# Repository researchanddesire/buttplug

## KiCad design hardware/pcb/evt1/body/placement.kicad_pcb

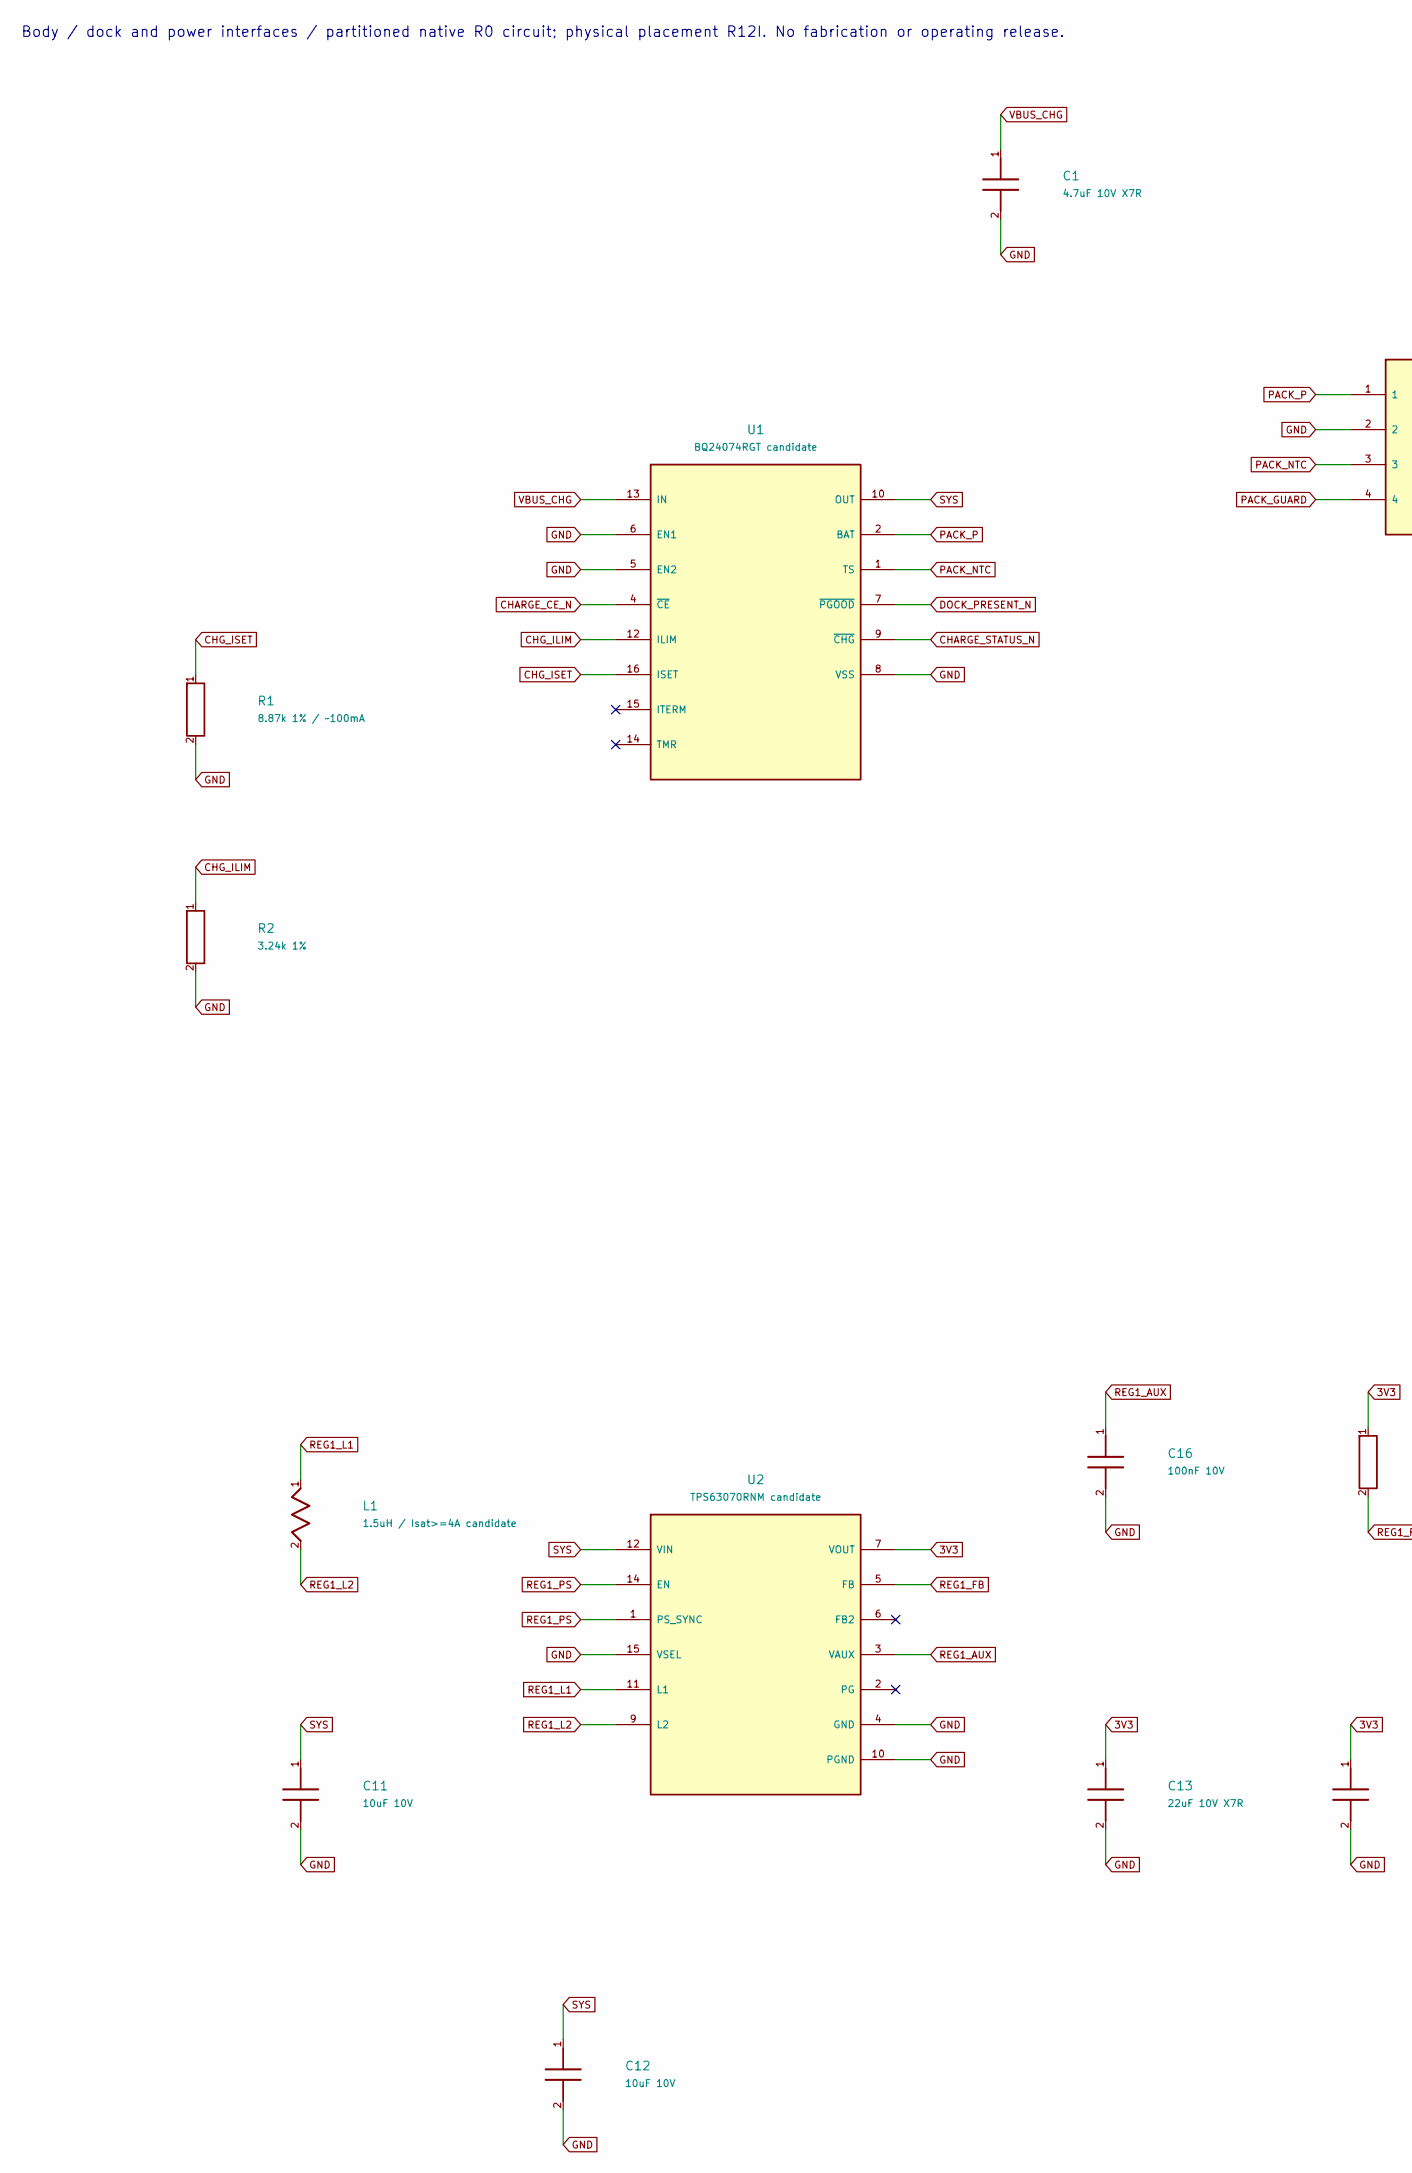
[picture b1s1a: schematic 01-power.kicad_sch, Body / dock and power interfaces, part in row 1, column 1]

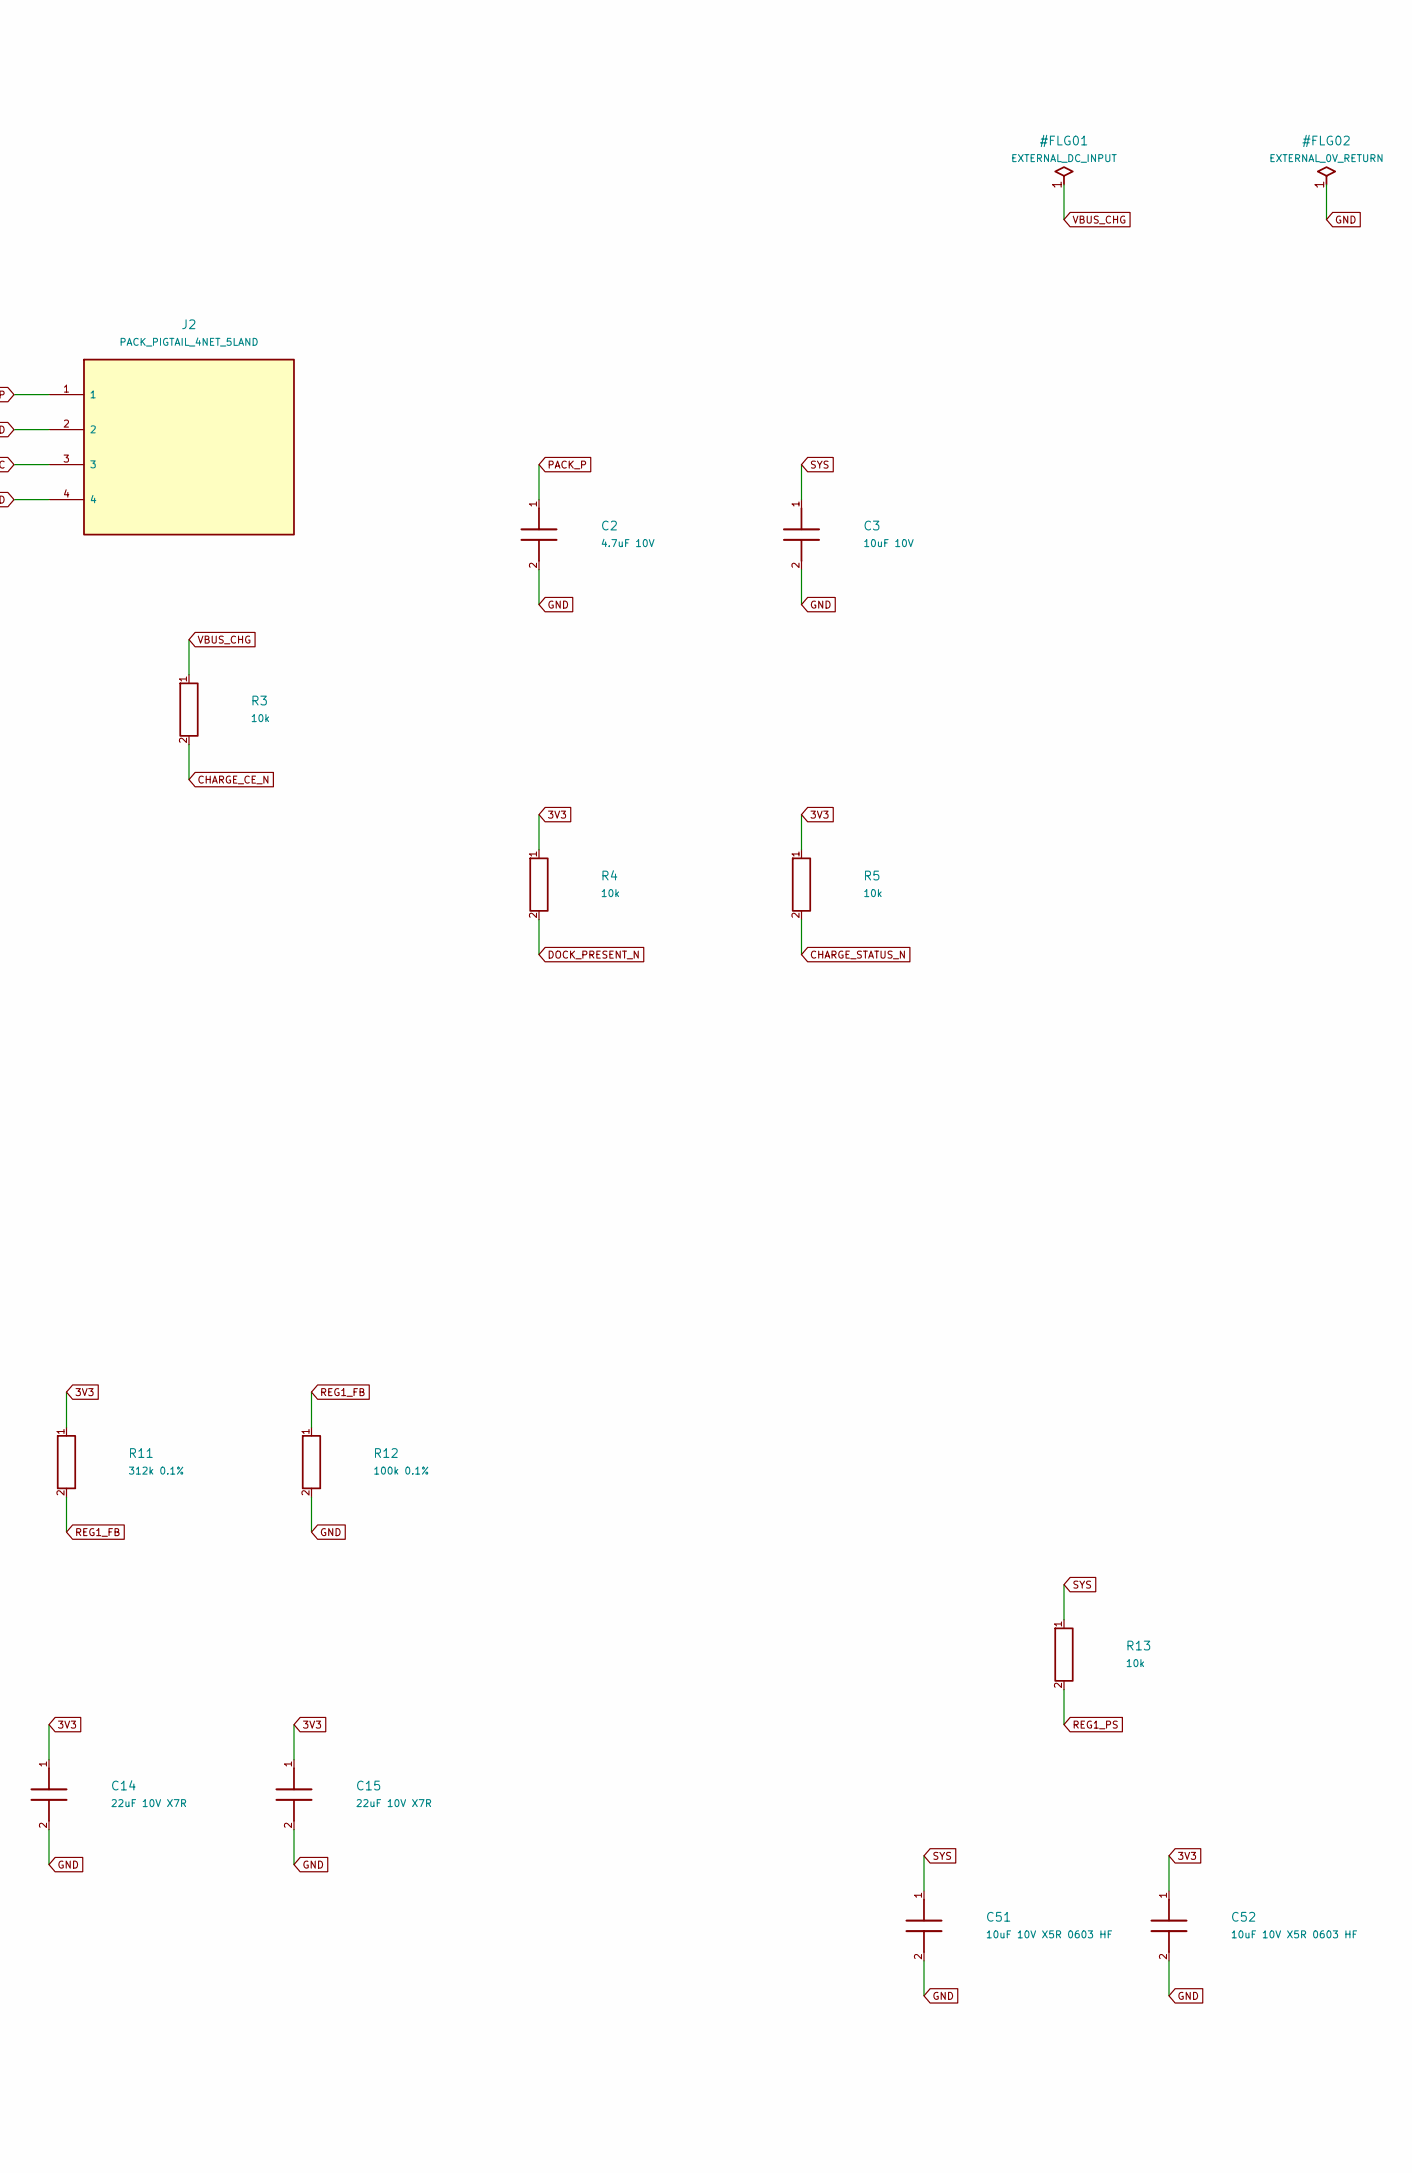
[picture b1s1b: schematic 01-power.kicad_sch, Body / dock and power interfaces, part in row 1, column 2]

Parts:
C1: 4.7uF 10V X7R; Murata_GRM21_0805_Reflow
C2: 4.7uF 10V; Murata_GRM21_0805_Reflow
C3, C11, C12: 10uF 10V; Murata_GRM21_0805_Reflow
C13, C14, C15: 22uF 10V X7R; Murata_GRM31_1206_Reflow
C16: 100nF 10V; Murata_GRM18_0603_Reflow
C51, C52: 10uF 10V X5R 0603 HF; TDK_C1608_0603_Reflow
J2: PACK_PIGTAIL_4NET_5LAND; Pack_Pigtail_4Net_5Land
L1: 1.5uH / Isat>=4A candidate; L_Coilcraft_XxL4020
R1: 8.87k 1% / ~100mA; R_0402_1005Metric
R2: 3.24k 1%; R_0402_1005Metric
R3, R4, R5: 10k; R_0402_1005Metric
R11: 312k 0.1%; Vishay_TNPW0603_IEC_Reflow
R12: 100k 0.1%; Vishay_TNPW0603_IEC_Reflow
R13: 10k; Vishay_TNPW0603_IEC_Reflow
U1: BQ24074RGT candidate; TI_RGT0016C_3x3mm_BQ24074_EP1.68mm
U2: TPS63070RNM candidate; TI_RNM0015A_2.5x3mm_TPS63070

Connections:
3V3: C13.1, C14.1, C15.1, C52.1, R4.1, R5.1, R11.1, U2.7 (VOUT), U2.8 (VOUT); also elsewhere on the board
CHARGE_CE_N: R3.2, U1.4 (~CE); also elsewhere on the board
CHARGE_STATUS_N: R5.2, U1.9 (~CHG)
CHG_ILIM: R2.1, U1.12 (ILIM)
CHG_ISET: R1.1, U1.16 (ISET)
DOCK_PRESENT_N: R4.2, U1.7 (~PGOOD); also elsewhere on the board
GND: C1.2, C2.2, C3.2, C11.2, C12.2, C13.2, C14.2, C15.2, C16.2, C51.2, C52.2, J2.2, R1.2, R2.2, R12.2, U1.5 (EN2), U1.6 (EN1), U1.8 (VSS), U1.17 (EP), U2.4 (GND), U2.10 (PGND), U2.15 (VSEL); also elsewhere on the board
PACK_GUARD: J2.4; also elsewhere on the board
PACK_NTC: J2.3, U1.1 (TS)
PACK_P: C2.1, J2.1, U1.2 (BAT), U1.3 (BAT); also elsewhere on the board
REG1_AUX: C16.1, U2.3 (VAUX)
REG1_FB: R11.2, R12.1, U2.5 (FB)
REG1_L1: L1.1, U2.11 (L1)
REG1_L2: L1.2, U2.9 (L2)
REG1_PS: R13.2, U2.1 (PS_SYNC), U2.14 (EN)
SYS: C3.1, C11.1, C12.1, C51.1, R13.1, U1.10 (OUT), U1.11 (OUT), U2.12 (VIN), U2.13 (VIN); also elsewhere on the board
VBUS_CHG: C1.1, R3.1, U1.13 (IN); also elsewhere on the board

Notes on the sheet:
Body / dock and power interfaces / partitioned native R0 circuit; physical placement R12I. No fabrication or operating release.

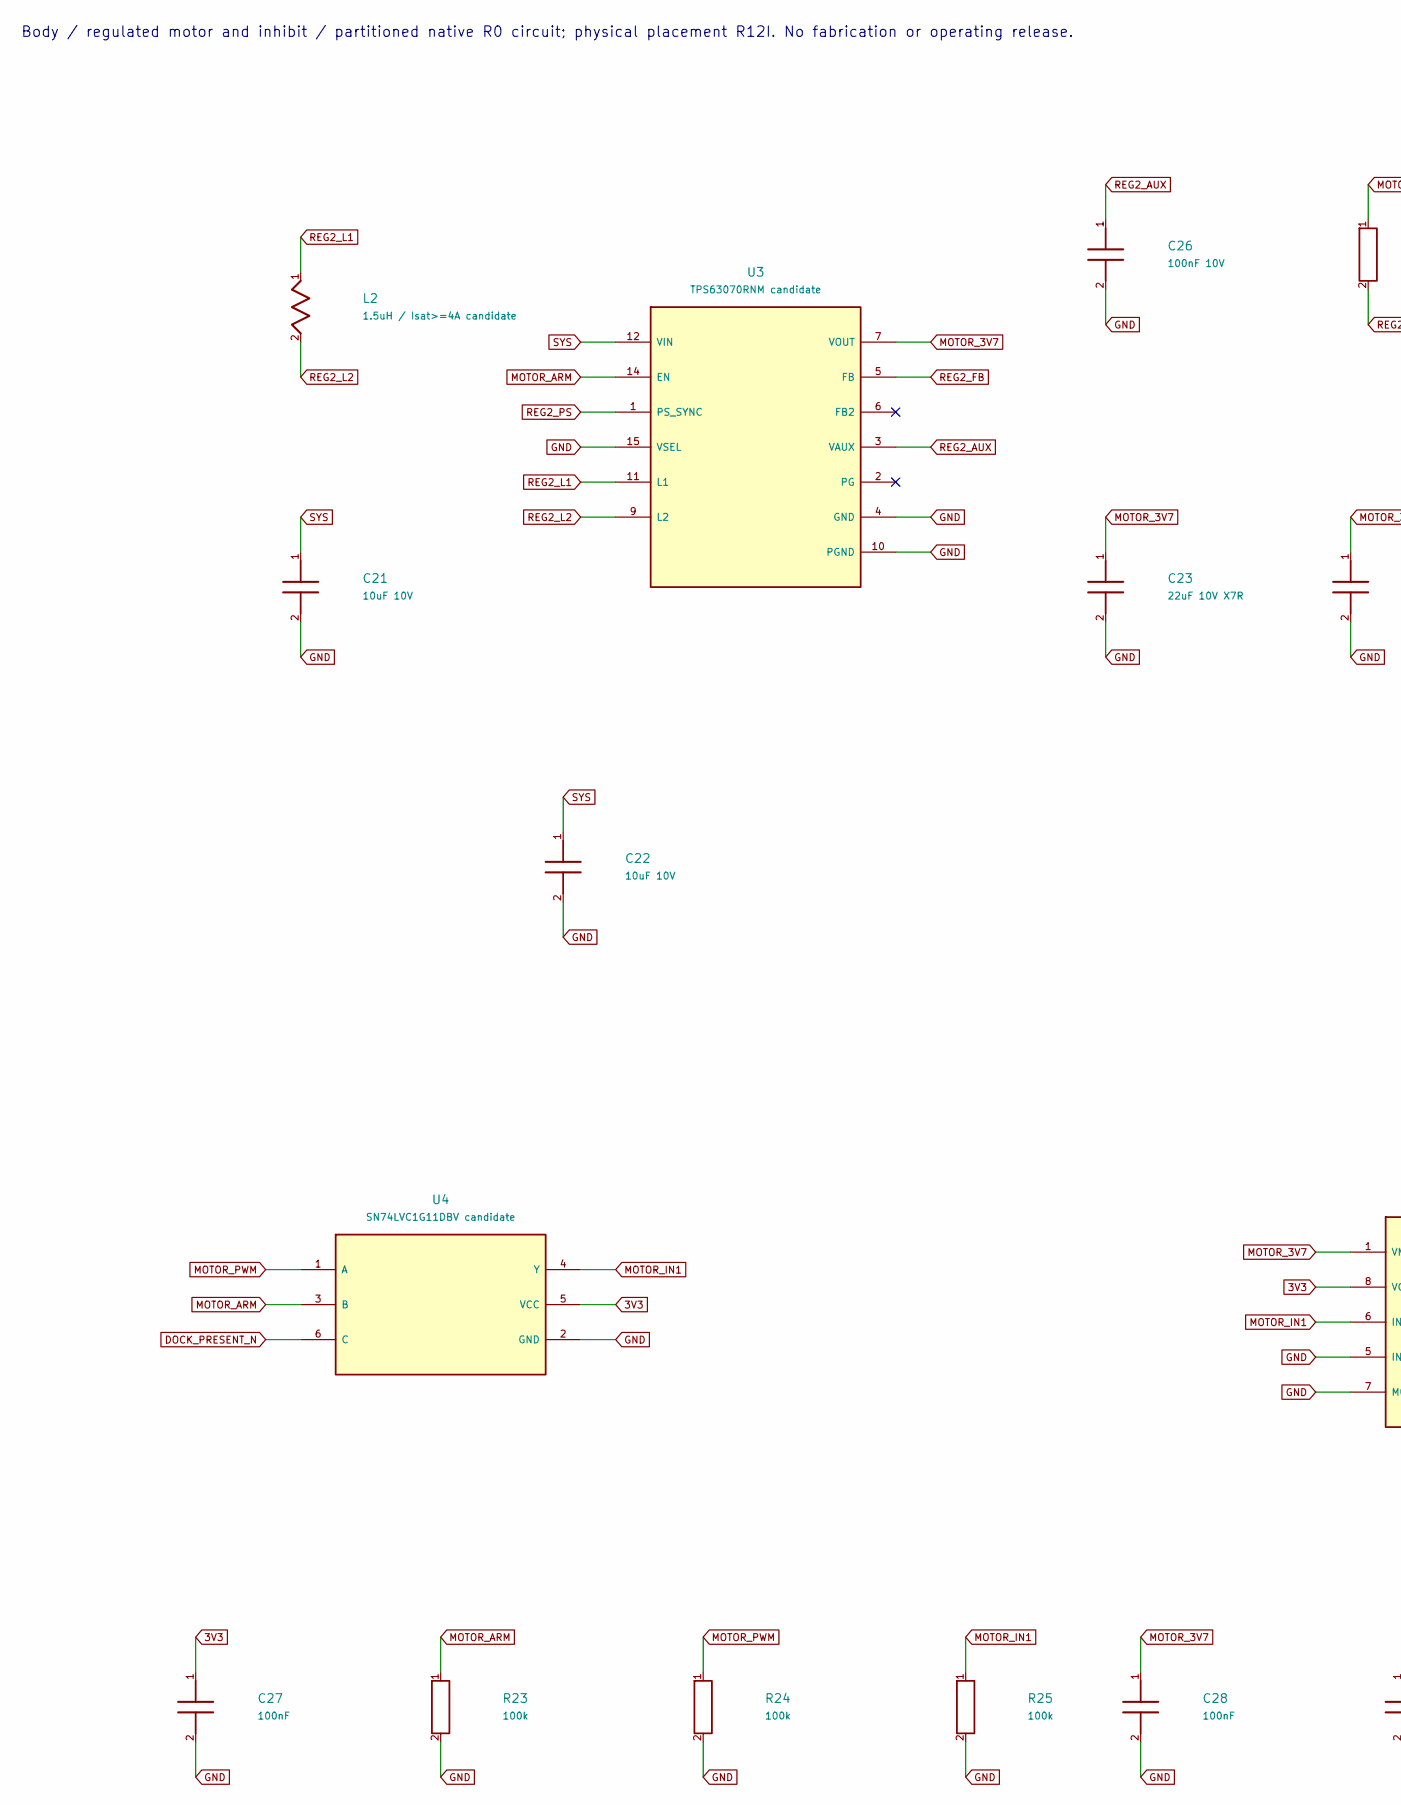
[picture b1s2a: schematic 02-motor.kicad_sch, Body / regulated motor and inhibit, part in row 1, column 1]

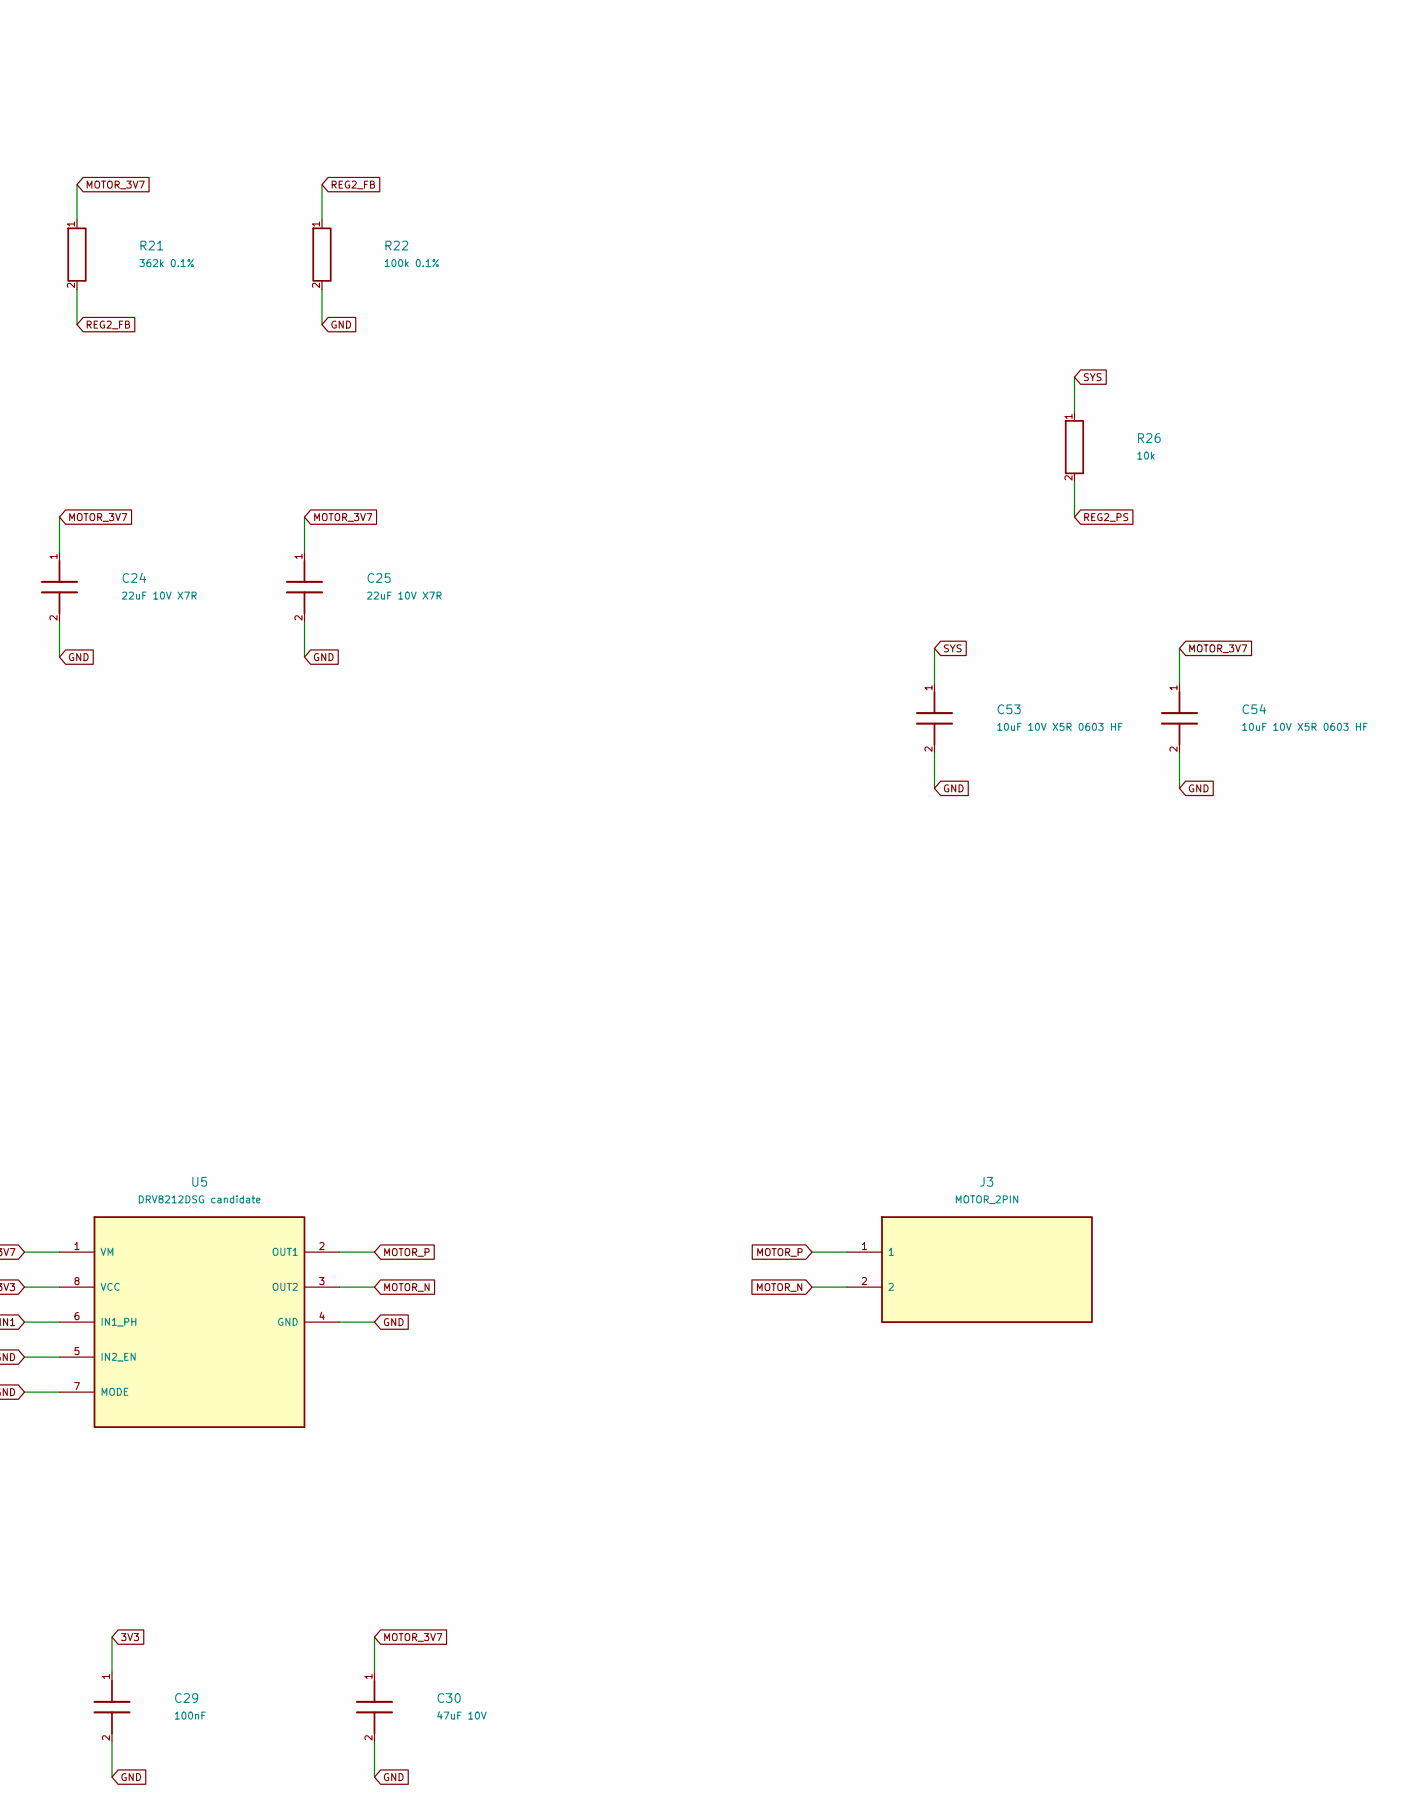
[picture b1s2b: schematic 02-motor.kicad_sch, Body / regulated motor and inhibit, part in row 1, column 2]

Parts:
C21, C22: 10uF 10V; Murata_GRM21_0805_Reflow
C23, C24, C25: 22uF 10V X7R; Murata_GRM31_1206_Reflow
C26: 100nF 10V; Murata_GRM18_0603_Reflow
C27: 100nF; Murata_GRM18_0603_Reflow
C28, C29: 100nF; C_0402_1005Metric
C30: 47uF 10V; Murata_GRM32_1210_Reflow
C53, C54: 10uF 10V X5R 0603 HF; TDK_C1608_0603_Reflow
J3: MOTOR_2PIN; JST_SH_SM02B-SRSS-TB_1x02-1MP_P1.00mm_Horizontal
L2: 1.5uH / Isat>=4A candidate; L_Coilcraft_XxL4020
R21: 362k 0.1%; Vishay_TNPW0805_IEC_Reflow
R22: 100k 0.1%; Vishay_TNPW0603_IEC_Reflow
R23, R24, R25: 100k; R_0402_1005Metric
R26: 10k; Vishay_TNPW0603_IEC_Reflow
U3: TPS63070RNM candidate; TI_RNM0015A_2.5x3mm_TPS63070
U4: SN74LVC1G11DBV candidate; SOT-23-6
U5: DRV8212DSG candidate; WSON-8-1EP_2x2mm_P0.5mm_EP0.9x1.6mm

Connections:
3V3: C27.1, C29.1, U4.5 (VCC), U5.8 (VCC); also elsewhere on the board
DOCK_PRESENT_N: U4.6 (C); also elsewhere on the board
GND: C21.2, C22.2, C23.2, C24.2, C25.2, C26.2, C27.2, C28.2, C29.2, C30.2, C53.2, C54.2, R22.2, R23.2, R24.2, R25.2, U3.4 (GND), U3.10 (PGND), U3.15 (VSEL), U4.2 (GND), U5.4 (GND), U5.5 (IN2_EN), U5.7 (MODE), U5.9 (EP); also elsewhere on the board
MOTOR_3V7: C23.1, C24.1, C25.1, C28.1, C30.1, C54.1, R21.1, U3.7 (VOUT), U3.8 (VOUT), U5.1 (VM)
MOTOR_ARM: R23.1, U3.14 (EN), U4.3 (B); also elsewhere on the board
MOTOR_IN1: R25.1, U4.4 (Y), U5.6 (IN1_PH)
MOTOR_N: J3.2, U5.3 (OUT2)
MOTOR_P: J3.1, U5.2 (OUT1)
MOTOR_PWM: R24.1, U4.1 (A); also elsewhere on the board
REG2_AUX: C26.1, U3.3 (VAUX)
REG2_FB: R21.2, R22.1, U3.5 (FB)
REG2_L1: L2.1, U3.11 (L1)
REG2_L2: L2.2, U3.9 (L2)
REG2_PS: R26.2, U3.1 (PS_SYNC)
SYS: C21.1, C22.1, C53.1, R26.1, U3.12 (VIN), U3.13 (VIN); also elsewhere on the board

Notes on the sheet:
Body / regulated motor and inhibit / partitioned native R0 circuit; physical placement R12I. No fabrication or operating release.

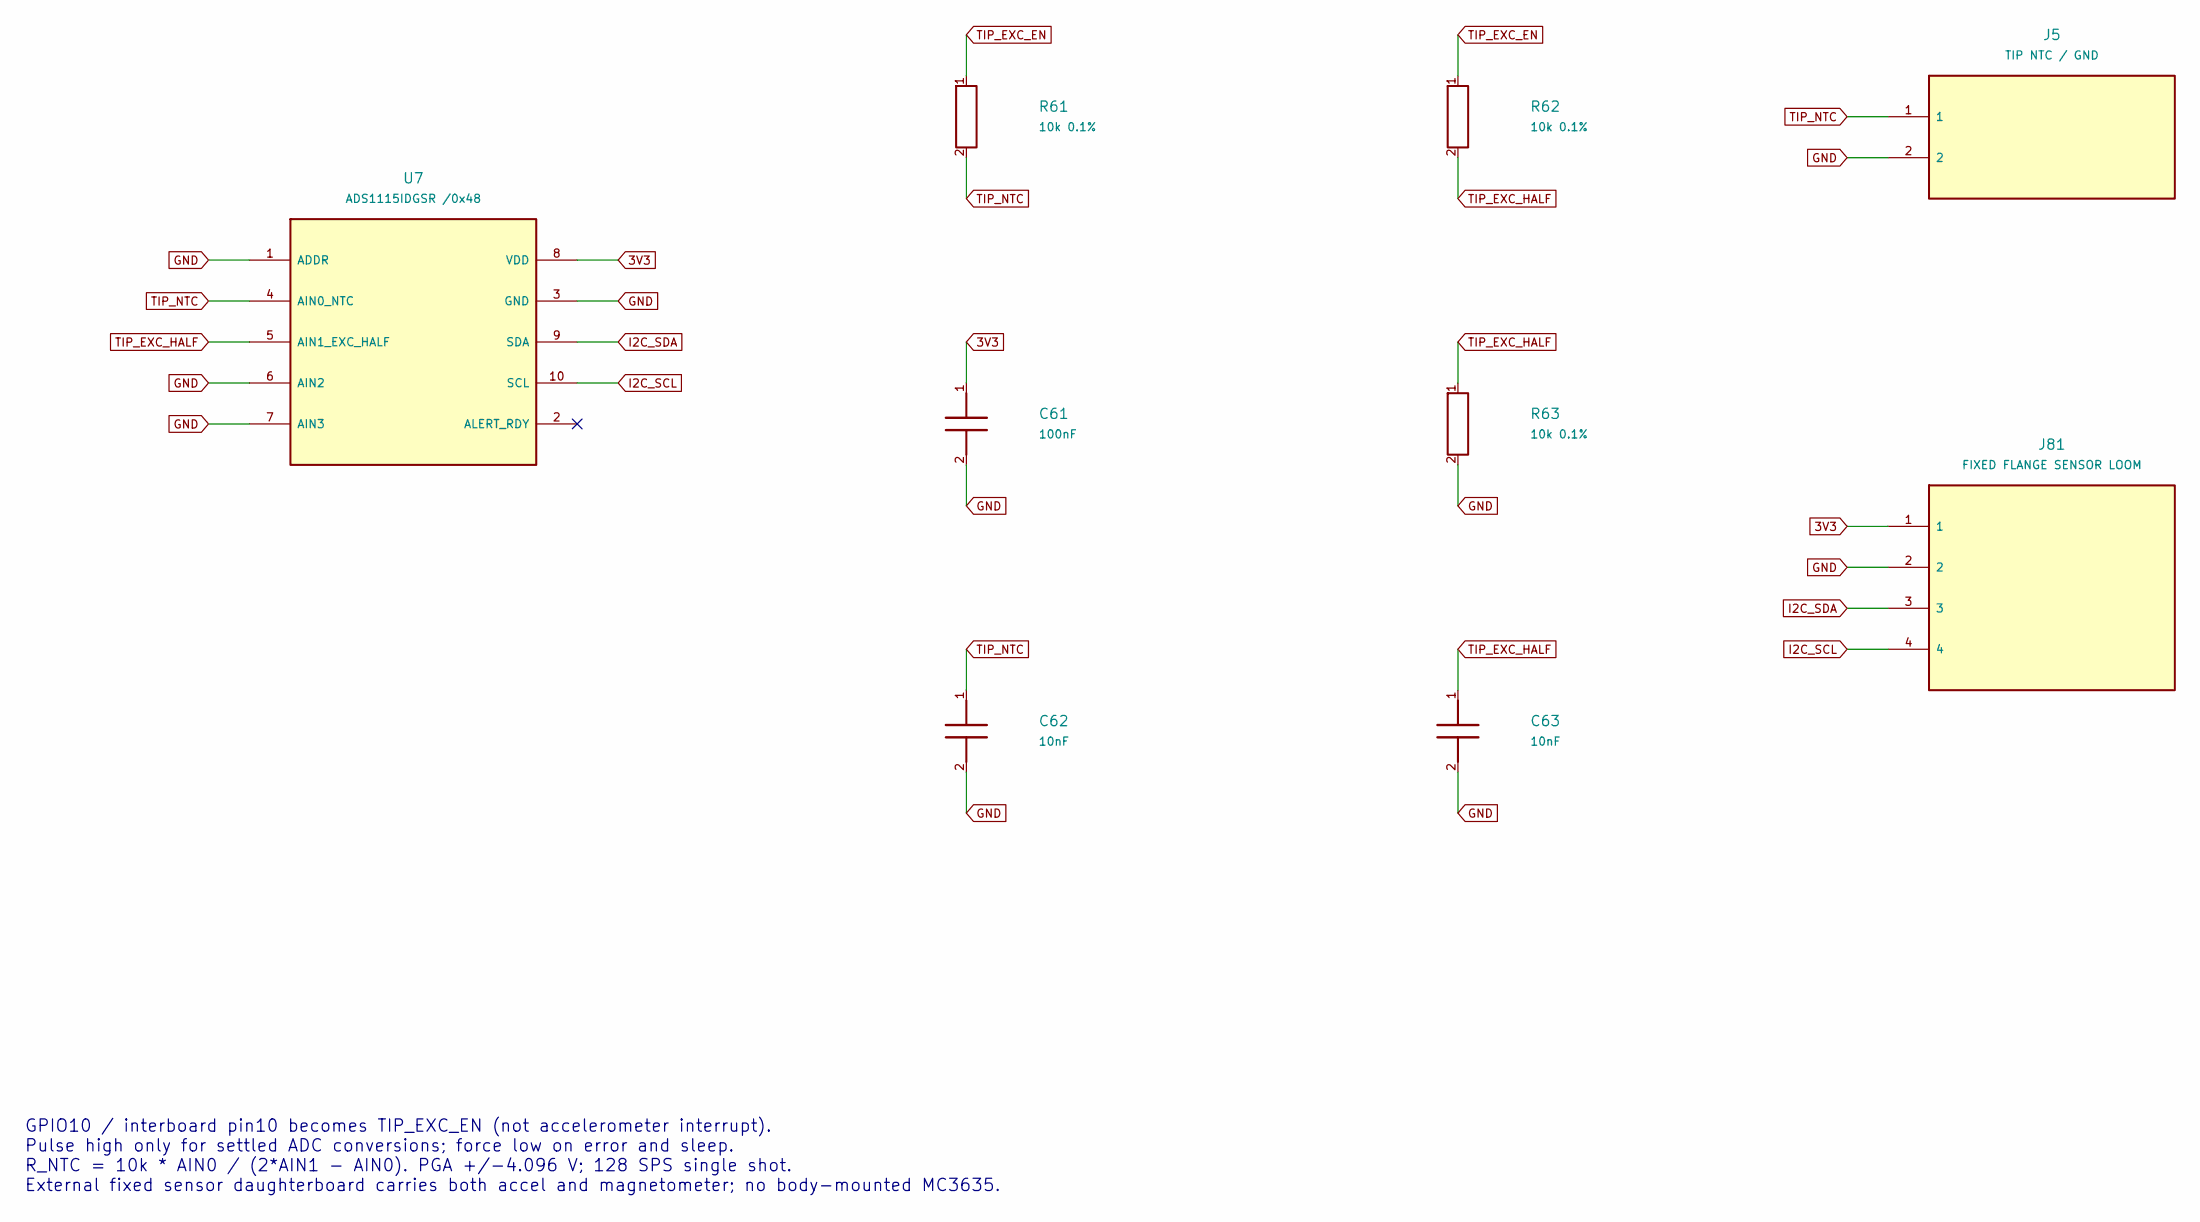
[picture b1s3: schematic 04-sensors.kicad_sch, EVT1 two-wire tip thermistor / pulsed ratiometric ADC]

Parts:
C61: 100nF; C_0402_1005Metric
C62, C63: 10nF; C_0402_1005Metric
J5: TIP NTC / GND; JST_SH_BM02B-SRSS-TB_1x02-1MP_P1.00mm_Vertical
J81: FIXED FLANGE SENSOR LOOM; Sensor_Loom_4Land
R61, R62, R63: 10k 0.1%; R_0402_1005Metric
U7: ADS1115IDGSR /0x48; VSSOP-10_3x3mm_P0.5mm

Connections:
3V3: C61.1, J81.1, U7.8 (VDD); also elsewhere on the board
GND: C61.2, C62.2, C63.2, J5.2, J81.2, R63.2, U7.1 (ADDR), U7.3 (GND), U7.6 (AIN2), U7.7 (AIN3); also elsewhere on the board
I2C_SCL: J81.4, U7.10 (SCL); also elsewhere on the board
I2C_SDA: J81.3, U7.9 (SDA); also elsewhere on the board
TIP_EXC_EN: R61.1, R62.1; also elsewhere on the board
TIP_EXC_HALF: C63.1, R62.2, R63.1, U7.5 (AIN1_EXC_HALF)
TIP_NTC: C62.1, J5.1, R61.2, U7.4 (AIN0_NTC)

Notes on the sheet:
GPIO10 / interboard pin10 becomes TIP_EXC_EN (not accelerometer interrupt). Pulse high only for settled ADC conversions; force low on error and sleep. R_NTC = 10k * AIN0 / (2*AIN1 - AIN0). PGA +/-4.096 V; 128 SPS single shot. External fixed sensor daughterboard carries both accel and magnetometer; 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

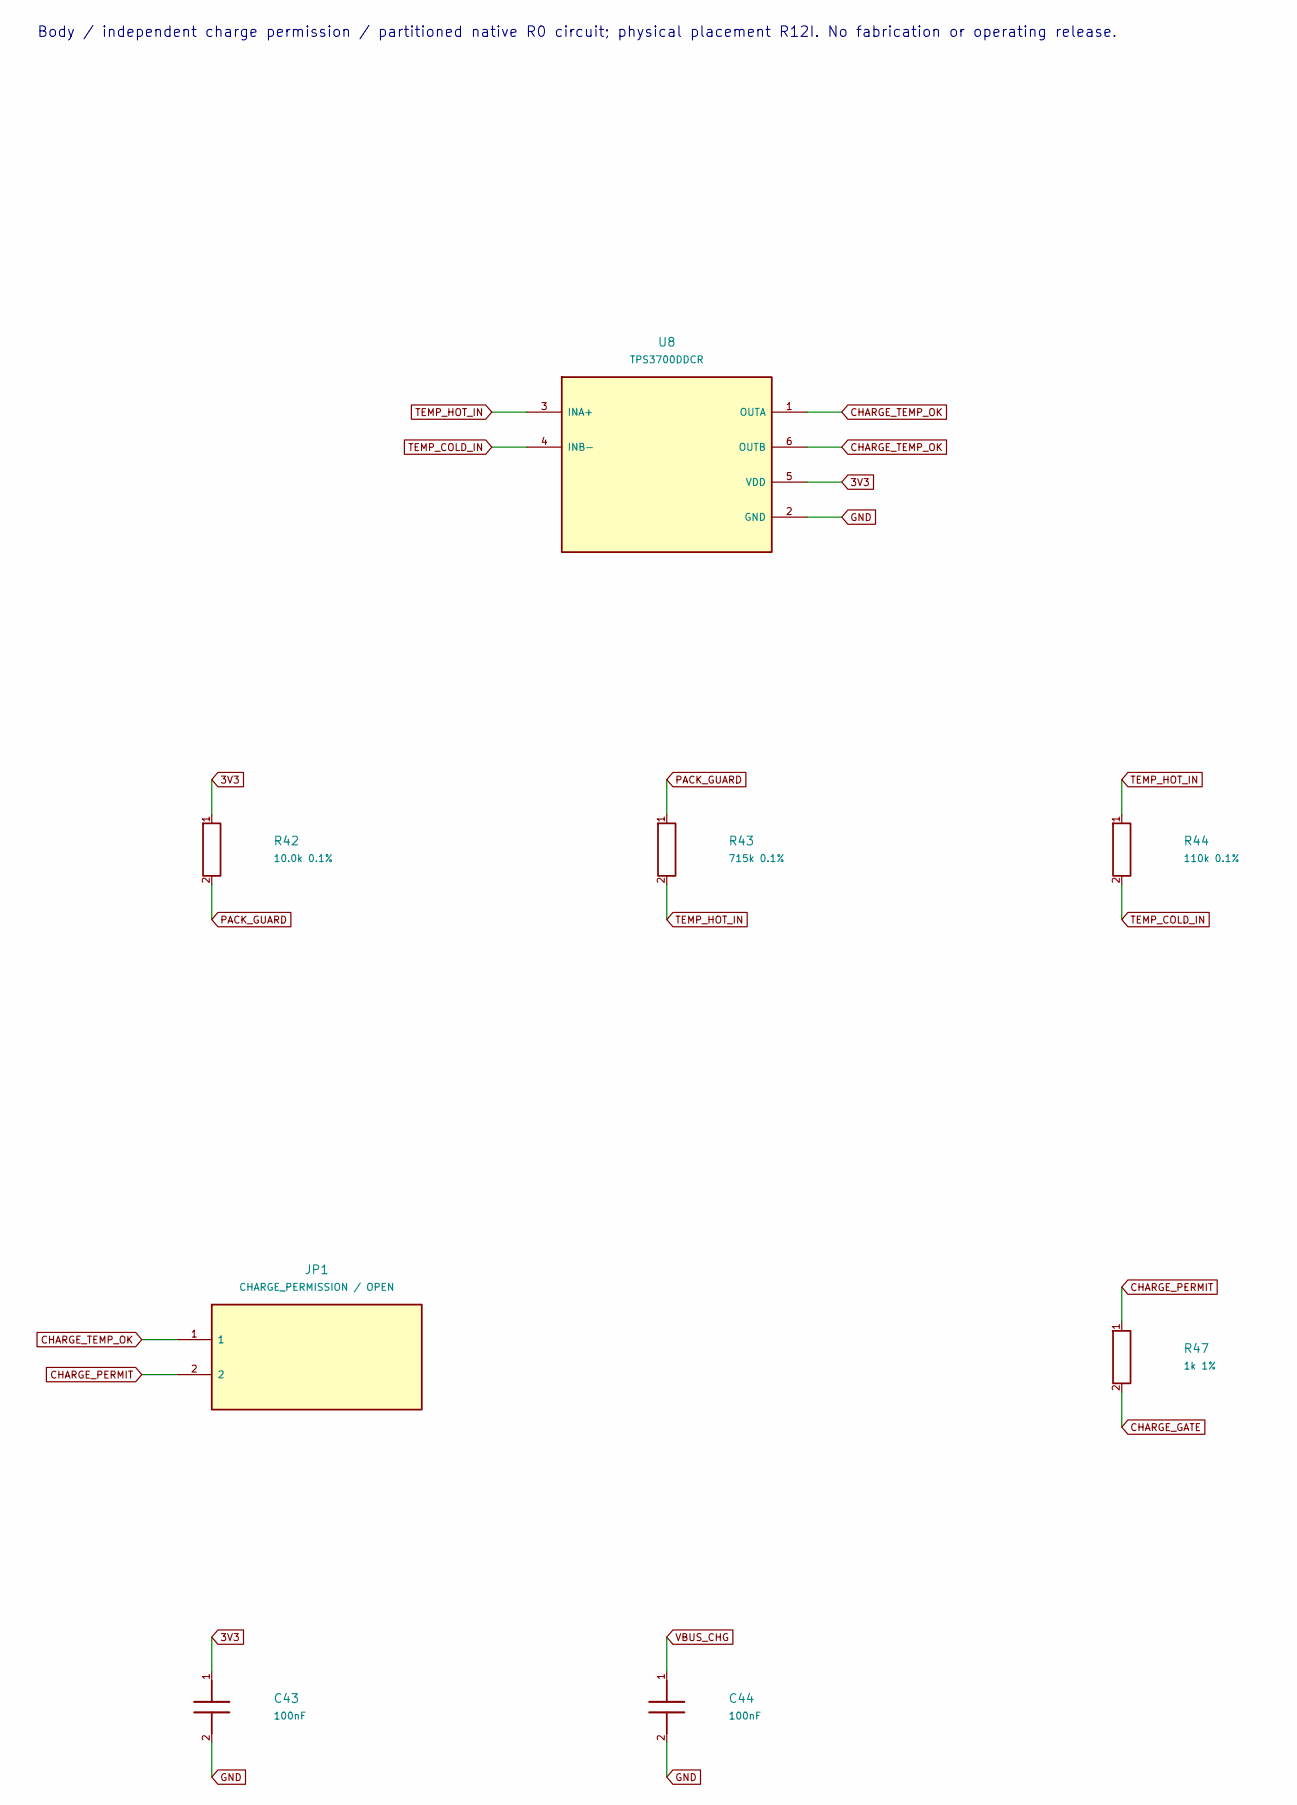
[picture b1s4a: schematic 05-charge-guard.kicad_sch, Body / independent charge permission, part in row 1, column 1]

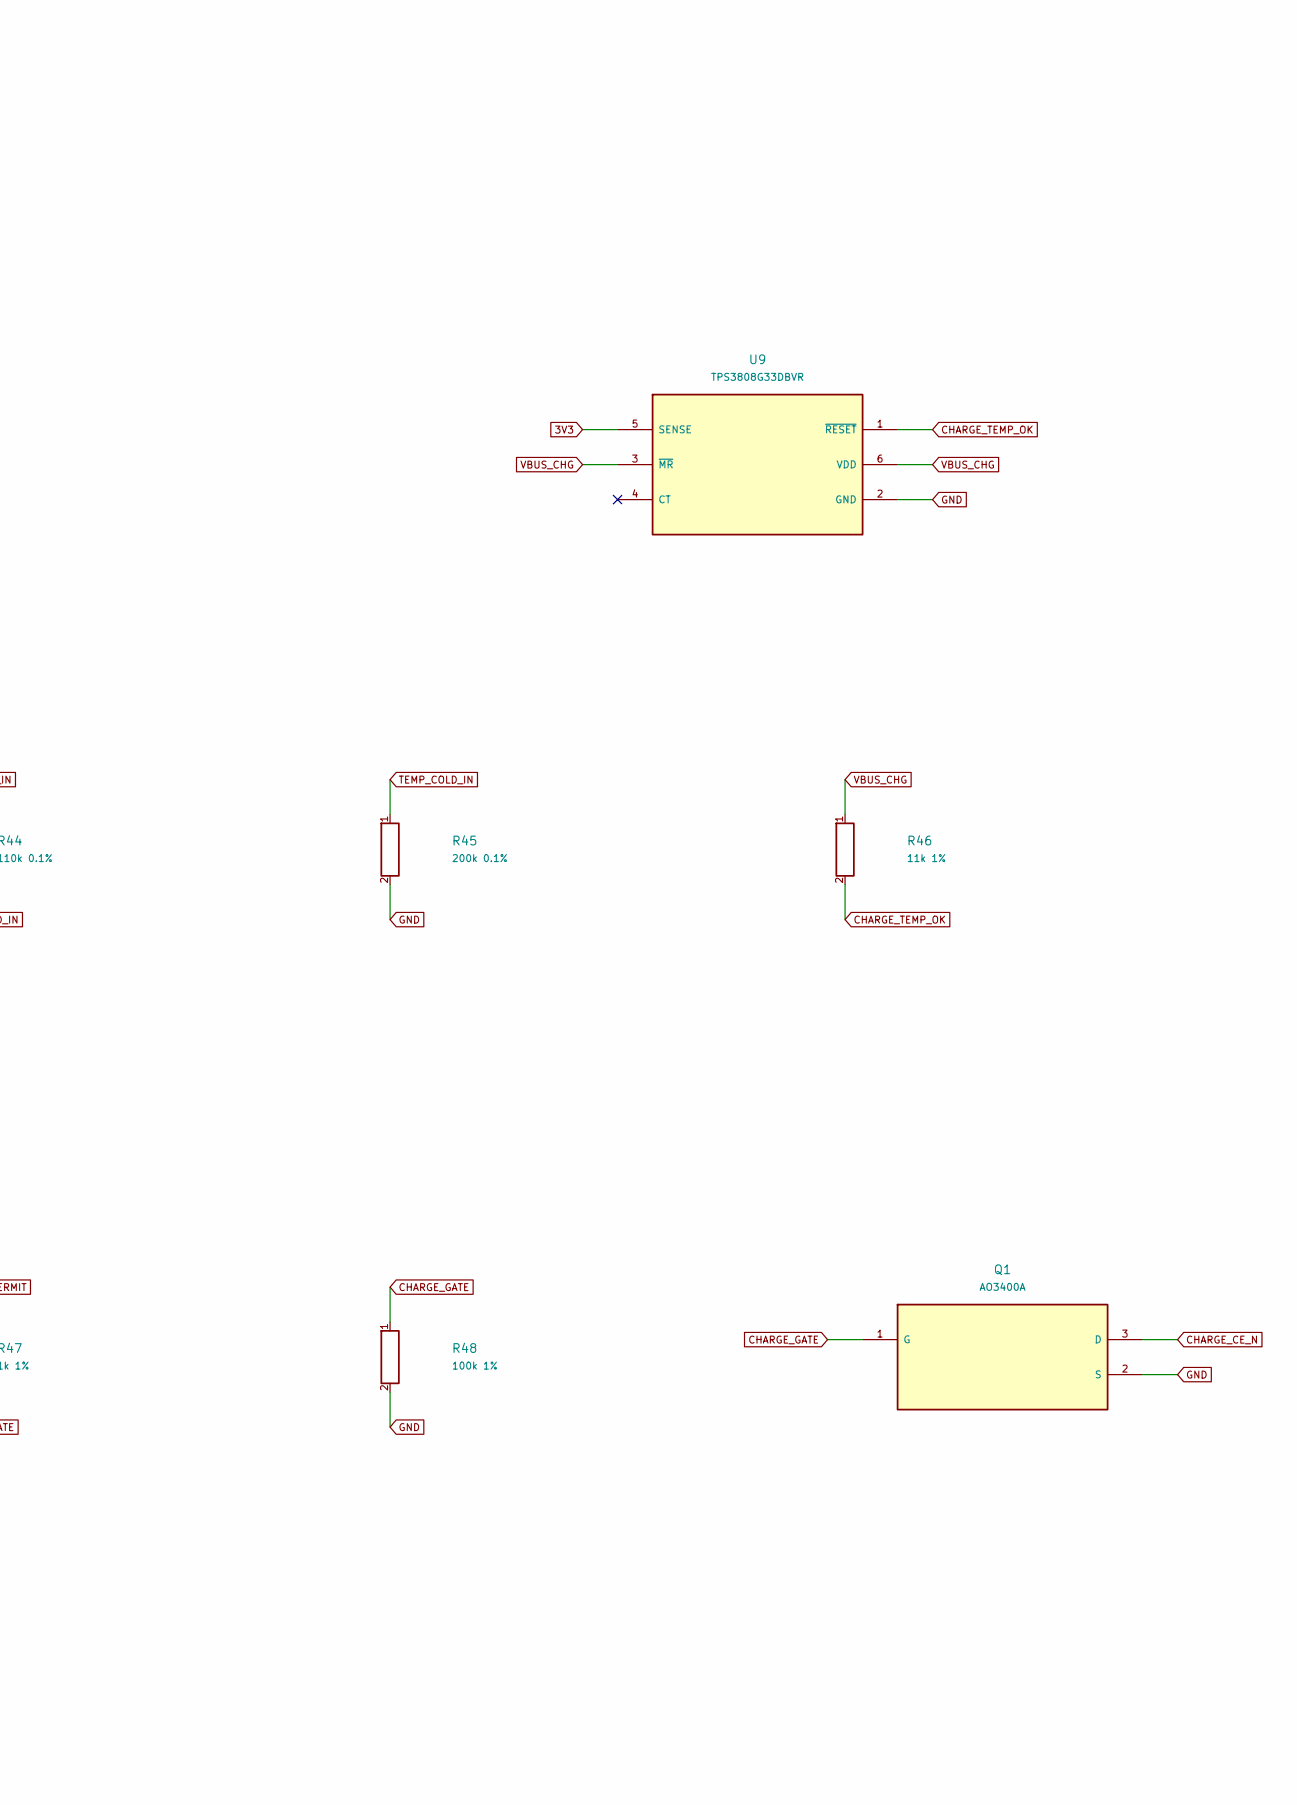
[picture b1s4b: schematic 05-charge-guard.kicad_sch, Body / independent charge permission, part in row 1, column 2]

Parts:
C43, C44: 100nF; Murata_GRM18_0603_Reflow
JP1: CHARGE_PERMISSION / OPEN; SolderJumper-2_P1.3mm_Open_RoundedPad1.0x1.5mm
Q1: AO3400A; SOT-23
R42: 10.0k 0.1%; R_0402_1005Metric
R43: 715k 0.1%; Vishay_TNPW0805_IEC_Reflow
R44: 110k 0.1%; Vishay_TNPW0603_IEC_Reflow
R45: 200k 0.1%; Vishay_TNPW0603_IEC_Reflow
R46: 11k 1%; R_0402_1005Metric
R47: 1k 1%; R_0402_1005Metric
R48: 100k 1%; R_0402_1005Metric
U8: TPS3700DDCR; TSOT-23-6
U9: TPS3808G33DBVR; SOT-23-6

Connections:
3V3: C43.1, R42.1, U8.5 (VDD), U9.5 (SENSE); also elsewhere on the board
CHARGE_CE_N: Q1.3 (D); also elsewhere on the board
CHARGE_GATE: Q1.1 (G), R47.2, R48.1
CHARGE_PERMIT: JP1.2, R47.1
CHARGE_TEMP_OK: JP1.1, R46.2, U8.1 (OUTA), U8.6 (OUTB), U9.1 (~RESET)
GND: C43.2, C44.2, Q1.2 (S), R45.2, R48.2, U8.2 (GND), U9.2 (GND); also elsewhere on the board
PACK_GUARD: R42.2, R43.1; also elsewhere on the board
TEMP_COLD_IN: R44.2, R45.1, U8.4 (INB-)
TEMP_HOT_IN: R43.2, R44.1, U8.3 (INA+)
VBUS_CHG: C44.1, R46.1, U9.3 (~MR), U9.6 (VDD); also elsewhere on the board

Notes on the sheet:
Body / independent charge permission / partitioned native R0 circuit; physical placement R12I. No fabrication or operating release.
